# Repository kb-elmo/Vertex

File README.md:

# Vertex

[![CC BY-NC-SA 4.0][cc-by-nc-sa-shield]][cc-by-nc-sa]

### 3D printed Vortex 40% inspired screwless exterior, top-mount keyboard

### This design has some flaws!
#### Use at your own risk

---

[STEP files for the case](case/)

[KiCAD PCB files](pcb/)

[Gerbers for PCB production](pcb/gerbers/)

[JLCPCB BOM](pcb/fab/vertex_bom_jlc.csv)

[JLCPCB CPL](pcb/fab/vertex_cpl_jlc.csv)

[Vial-QMK firmware](firmware/)

---

This work is licensed under a
[Creative Commons Attribution-NonCommercial-ShareAlike 4.0 International License][cc-by-nc-sa].

[![CC BY-NC-SA 4.0][cc-by-nc-sa-image]][cc-by-nc-sa]

[cc-by-nc-sa]: http://creativecommons.org/licenses/by-nc-sa/4.0/
[cc-by-nc-sa-image]: https://licensebuttons.net/l/by-nc-sa/4.0/88x31.png
[cc-by-nc-sa-shield]: https://img.shields.io/badge/License-CC%20BY--NC--SA%204.0-lightgrey.svg

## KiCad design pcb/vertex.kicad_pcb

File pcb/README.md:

# Vertex PCB

### Features

- Powered by an Atmega32u2
- Basic ESD and overvoltage protection
- USB type-C port for a detachable cable
- Multiple layout options (see below)
- Fully programmable using [QMK](https://qmk.fm) and [Vial](https://get.vial.today)

---

### Supported layouts

The two different lengths spacebars can be swapped.

---

### Preview

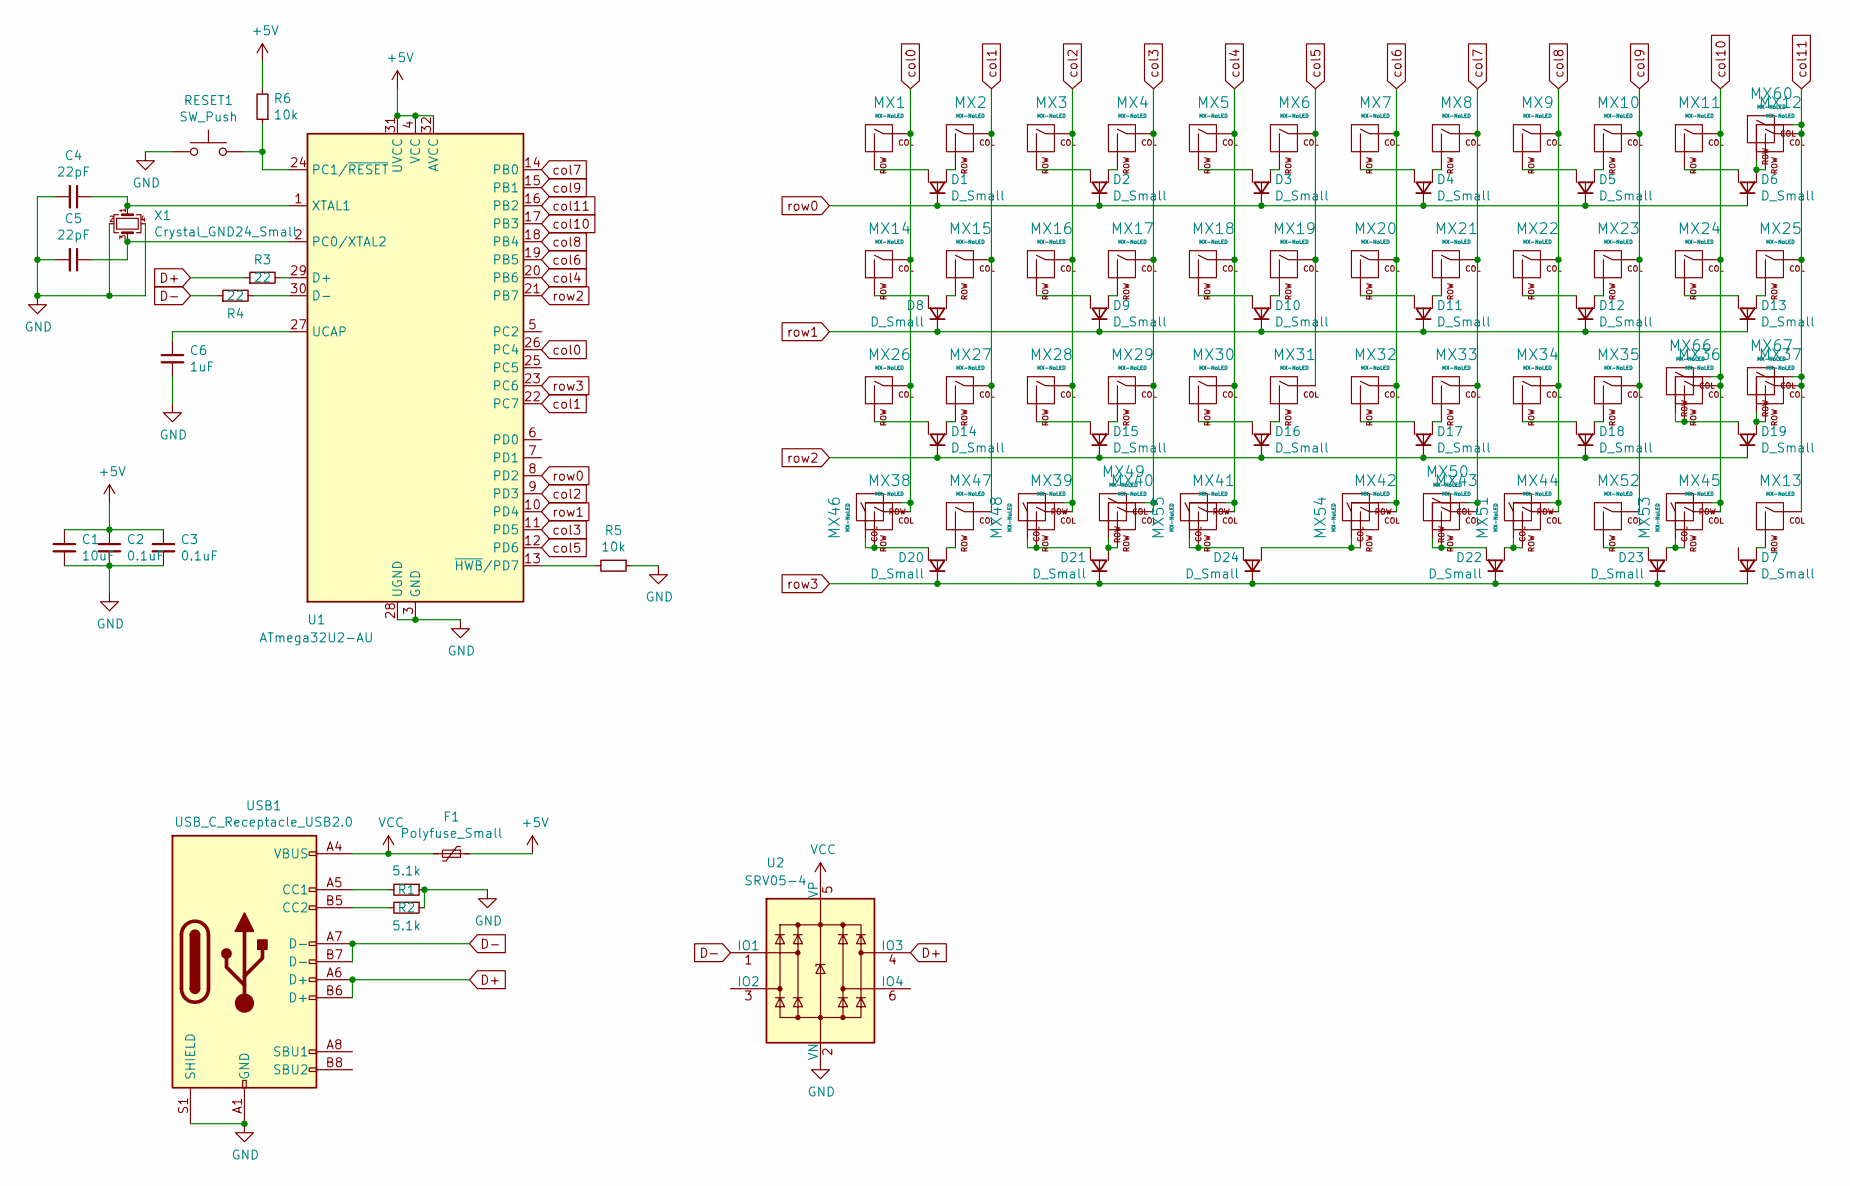
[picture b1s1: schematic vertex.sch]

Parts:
C1: 10uF; C_0805_2012Metric; LCSC C91245
C2, C3: 0.1uF; C_0805_2012Metric; LCSC C49678
C4, C5: 22pF; C_0805_2012Metric; LCSC C1804
C6: 1uF; C_0805_2012Metric; LCSC C28323
D1, D2, D3, D4, D5, D6, D7, D8, D9, D10, D11, D12, D13, D14, D15, D16, D17, D18, D19, D20, D21, D22, D23, D24: D_Small; D_SOT-23_ANK_norm; LCSC C68978
F1: Polyfuse_Small; Fuse_1206_3216Metric; LCSC C69688
MX1, MX2, MX3, MX4, MX5, MX6, MX7, MX8, MX9, MX10, MX11, MX12, MX13, MX15, MX16, MX17, MX18, MX19, MX20, MX21, MX22, MX23, MX24, MX27, MX28, MX29, MX30, MX31, MX32, MX33, MX34, MX35, MX36, MX46, MX47, MX48, MX49, MX50, MX51, MX52, MX53, MX67: MX-NoLED; MXOnly-1U-NoLED
MX14, MX37, MX39, MX40, MX43, MX44, MX66: MX-NoLED; MXOnly-1.25U-NoLED
MX25, MX26: MX-NoLED; MXOnly-1.75U-NoLED
MX38, MX45: MX-NoLED; MXOnly-1.5U-NoLED
MX41, MX54: MX-NoLED; MXOnly-2.75U-ReversedStabilizers-NoLED
MX42, MX55: MX-NoLED; MXOnly-2.25U-ReversedStabilizers-NoLED
MX60: MX-NoLED; MXOnly-2U-NoLED
R1, R2: 5.1k; R_0805_2012Metric; LCSC C27834
R3, R4: 22; R_0805_2012Metric; LCSC C17561
R5, R6: 10k; R_0805_2012Metric; LCSC C17414
RESET1: SW_Push; SW_SPST_TL3342; LCSC C318884
U1: ATmega32U2-AU; TQFP-32_7x7mm_P0.8mm; LCSC C618733
U2: SRV05-4; SOT-23-6; LCSC C85364
USB1: USB_C_Receptacle_USB2.0; USB_C_Receptacle_HRO_TYPE-C-31-M-12; LCSC C165948
X1: Crystal_GND24_Small; Crystal_SMD_3225-4Pin_3.2x2.5mm; LCSC C13738

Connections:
+5V: C1.1, C2.1, C3.1, F1.1, R6.2, U1.4 (VCC), U1.31 (UVCC), U1.32 (AVCC)
D+: R3.1, U2.4 (IO3), USB1.A6 (D+), USB1.B6 (D+)
D-: R4.1, U2.1 (IO1), USB1.A7 (D-), USB1.B7 (D-)
GND: C1.2, C2.2, C3.2, C4.2, C5.2, C6.2, R1.1, R2.1, R5.1, RESET1.1, U1.3 (GND), U1.28 (UGND), U2.2 (VN), USB1.A1 (GND), USB1.A12 (GND), USB1.B1 (GND), USB1.B12 (GND), USB1.S1 (SHIELD), X1.2, X1.4; also elsewhere on the board
unnamed: C4.1, U1.1 (XTAL1), X1.1
unnamed: C5.1, U1.2 (PC0/XTAL2), X1.3
unnamed: C6.1, U1.27 (UCAP)
unnamed: D1.2 (A1), MX1.2 (ROW)
unnamed: D1.3 (A2), MX2.2 (ROW)
unnamed: D2.2 (A1), MX3.2 (ROW)
unnamed: D2.3 (A2), MX4.2 (ROW)
unnamed: D3.2 (A1), MX5.2 (ROW)
unnamed: D3.3 (A2), MX6.2 (ROW)
unnamed: D4.2 (A1), MX7.2 (ROW)
unnamed: D4.3 (A2), MX8.2 (ROW)
unnamed: D5.2 (A1), MX9.2 (ROW)
unnamed: D5.3 (A2), MX10.2 (ROW)
unnamed: D6.2 (A1), MX11.2 (ROW)
unnamed: D6.3 (A2), MX12.2 (ROW), MX60.2 (ROW)
unnamed: D7.3 (A2), MX13.2 (ROW)
unnamed: D8.2 (A1), MX15.2 (ROW)
unnamed: D8.3 (A2), MX14.2 (ROW)
unnamed: D9.2 (A1), MX16.2 (ROW)
unnamed: D9.3 (A2), MX17.2 (ROW)
unnamed: D10.2 (A1), MX18.2 (ROW)
unnamed: D10.3 (A2), MX19.2 (ROW)
unnamed: D11.2 (A1), MX20.2 (ROW)
unnamed: D11.3 (A2), MX21.2 (ROW)
unnamed: D12.2 (A1), MX22.2 (ROW)
unnamed: D12.3 (A2), MX23.2 (ROW)
unnamed: D13.2 (A1), MX24.2 (ROW)
unnamed: D13.3 (A2), MX25.2 (ROW)
unnamed: D14.2 (A1), MX26.2 (ROW)
unnamed: D14.3 (A2), MX27.2 (ROW)
unnamed: D15.2 (A1), MX28.2 (ROW)
unnamed: D15.3 (A2), MX29.2 (ROW)
unnamed: D16.2 (A1), MX30.2 (ROW)
unnamed: D16.3 (A2), MX31.2 (ROW)
unnamed: D17.2 (A1), MX32.2 (ROW)
unnamed: D17.3 (A2), MX33.2 (ROW)
unnamed: D18.2 (A1), MX34.2 (ROW)
unnamed: D18.3 (A2), MX35.2 (ROW)
unnamed: D19.2 (A1), MX36.2 (ROW), MX66.2 (ROW)
unnamed: D19.3 (A2), MX37.2 (ROW), MX67.2 (ROW)
unnamed: D20.2 (A1), MX47.2 (ROW)
unnamed: D20.3 (A2), MX38.2 (ROW), MX46.1 (COL)
unnamed: D21.2 (A1), MX40.2 (ROW), MX49.2 (ROW)
unnamed: D21.3 (A2), MX39.2 (ROW), MX48.1 (COL)
unnamed: D22.2 (A1), MX44.2 (ROW), MX51.1 (COL)
unnamed: D22.3 (A2), MX43.2 (ROW), MX50.2 (ROW)
unnamed: D23.2 (A1), MX45.2 (ROW), MX53.1 (COL)
unnamed: D23.3 (A2), MX52.2 (ROW)
unnamed: D24.2 (A1), MX42.2 (ROW), MX54.1 (COL)
unnamed: D24.3 (A2), MX41.2 (ROW), MX55.1 (COL)
unnamed: R1.2, USB1.A5 (CC1)
unnamed: R2.2, USB1.B5 (CC2)
unnamed: R3.2, U1.29 (D+)
unnamed: R4.2, U1.30 (D-)
unnamed: R5.2, U1.13 (~HWB~/PD7)
unnamed 60: R6.1, RESET1.2, U1.24 (PC1/~RESET); also elsewhere on the board
VCC: F1.2, U2.5 (VP), USB1.A4 (VBUS), USB1.A9 (VBUS), USB1.B4 (VBUS), USB1.B9 (VBUS)
col0: MX1.1 (COL), MX14.1 (COL), MX26.1 (COL), MX38.1 (COL), MX46.2 (ROW), U1.26 (PC4)
col1: MX2.1 (COL), MX15.1 (COL), MX27.1 (COL), MX47.1 (COL), U1.22 (PC7)
col2: MX3.1 (COL), MX16.1 (COL), MX28.1 (COL), MX39.1 (COL), MX48.2 (ROW), U1.9 (PD3)
col3: MX4.1 (COL), MX17.1 (COL), MX29.1 (COL), MX40.1 (COL), MX49.1 (COL), U1.11 (PD5)
col4: MX5.1 (COL), MX18.1 (COL), MX30.1 (COL), MX41.1 (COL), MX55.2 (ROW), U1.20 (PB6)
col5: MX6.1 (COL), MX19.1 (COL), MX31.1 (COL), U1.12 (PD6)
col6: MX7.1 (COL), MX20.1 (COL), MX32.1 (COL), MX42.1 (COL), MX54.2 (ROW), U1.19 (PB5)
col7: MX8.1 (COL), MX21.1 (COL), MX33.1 (COL), MX43.1 (COL), MX50.1 (COL), U1.14 (PB0)
col8: MX9.1 (COL), MX22.1 (COL), MX34.1 (COL), MX44.1 (COL), MX51.2 (ROW), U1.18 (PB4)
col9: MX10.1 (COL), MX23.1 (COL), MX35.1 (COL), MX52.1 (COL), U1.15 (PB1)
col10: MX11.1 (COL), MX24.1 (COL), MX36.1 (COL), MX45.1 (COL), MX53.2 (ROW), MX66.1 (COL), U1.17 (PB3)
col11: MX12.1 (COL), MX13.1 (COL), MX25.1 (COL), MX37.1 (COL), MX60.1 (COL), MX67.1 (COL), U1.16 (PB2)
row0: D1.1 (K), D2.1 (K), D3.1 (K), D4.1 (K), D5.1 (K), D6.1 (K), U1.8 (PD2)
row1: D8.1 (K), D9.1 (K), D10.1 (K), D11.1 (K), D12.1 (K), D13.1 (K), U1.10 (PD4)
row2: D14.1 (K), D15.1 (K), D16.1 (K), D17.1 (K), D18.1 (K), D19.1 (K), U1.21 (PB7)
row3: D7.1 (K), D20.1 (K), D21.1 (K), D22.1 (K), D23.1 (K), D24.1 (K), U1.23 (PC6)

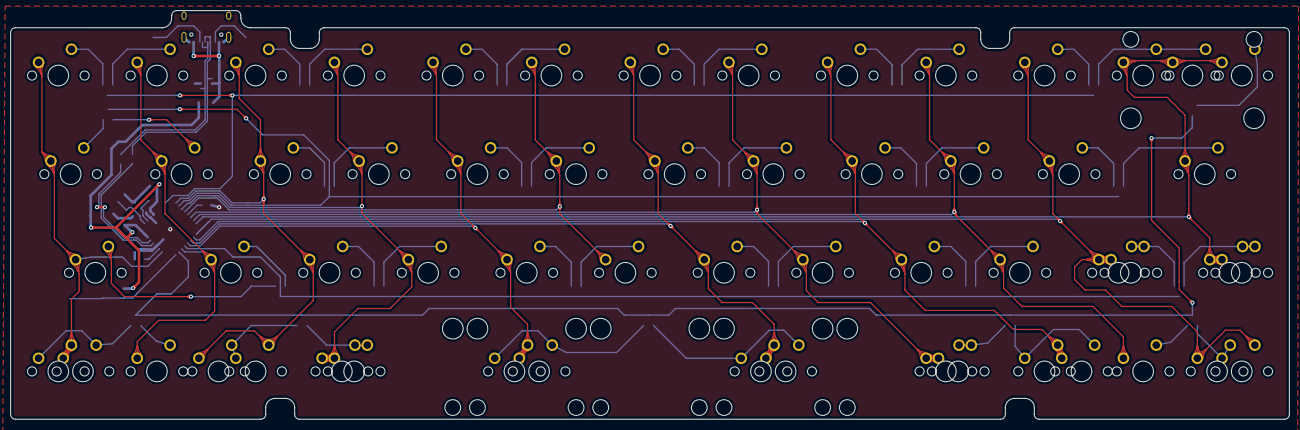
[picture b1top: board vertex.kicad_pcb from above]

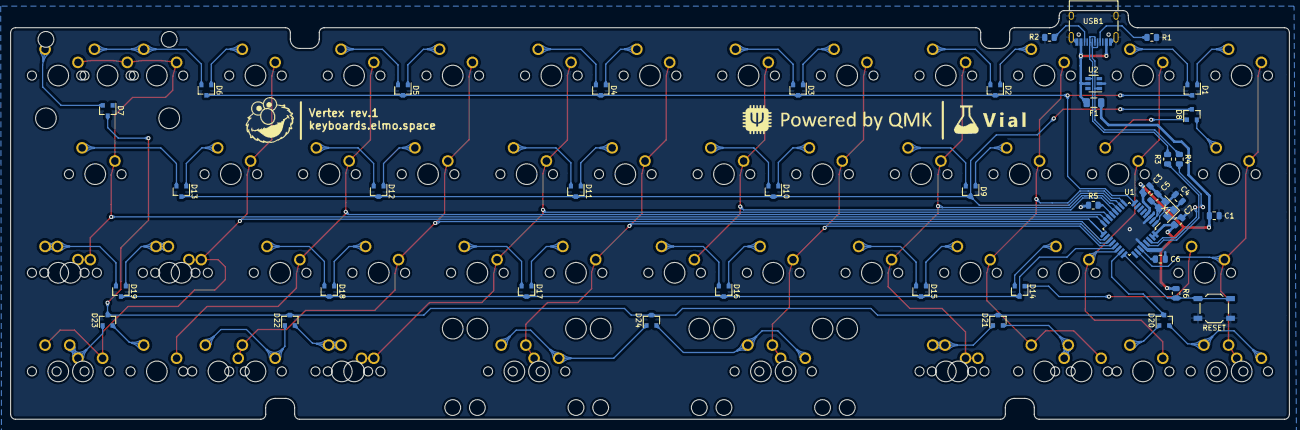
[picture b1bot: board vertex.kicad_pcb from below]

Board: 2 copper layers, 247.0 x 78.9 mm, 100 parts (42 on the bottom side), 77 nets.

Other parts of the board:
RESET: SW_Push; SW_SPST_TL3342

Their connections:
GND: RESET.1; also elsewhere on the board
unnamed 60: RESET.2; also elsewhere on the board

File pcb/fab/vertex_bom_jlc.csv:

"Comment","Designator","Footprint","LCSC Part #"
"10uF","C1","C_0805_2012Metric","C91245"
"0.1uF","C2,C3","C_0805_2012Metric","C49678"
"22pF","C4,C5","C_0805_2012Metric","C1804"
"1uF","C6","C_0805_2012Metric","C28323"
"D_Small","D5,D4,D3,D2,D6,D8,D12,D11,D10,D9,D13,D14,D18,D17,D16,D15,D19,D20,D22,D21,D23,D24,D7,D1","D_SOT-23_ANK_norm","C68978"
"Polyfuse_Small","F1","Fuse_1206_3216Metric","C69688"
"5.1k","R1,R2","R_0805_2012Metric","C27834"
"22","R3,R4","R_0805_2012Metric","C17561"
"10k","R5,R6","R_0805_2012Metric","C17414"
"SW_Push","RESET","SW_SPST_TL3342","C318884"
"ATmega32U2-AU","U1","TQFP-32_7x7mm_P0.8mm","C618733"
"SRV05-4","U2","SOT-23-6","C85364"
"USB_C_Receptacle_USB2.0","USB1","USB_C_Receptacle_HRO_TYPE-C-31-M-12","C165948"
"Crystal_GND24_Small","X1","Crystal_SMD_3225-4Pin_3.2x2.5mm","C13738"

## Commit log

2021-09-06 PCB finalized
2021-09-16 finalized PCB
2021-11-27 finalize repo layout
2021-11-27 update gerbers
